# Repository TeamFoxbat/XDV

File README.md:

# XDV
100% digital-to-digital video encoder inspired by existing projects for the Original Xbox. Currently no firmware released but is compatible with existing digital video encoding solutions.

## Installation Notes
The v1.0-1.4 Xbox boards have a big electrolytic cap next to the stock encoder that will interfere with installation. Recommendation is to replace with a S1206 10uF ceramic.

The ferite bead on the bottom right of the stock encoder must be removed. 

Notes for installing the power and SMBus harnesses to come soon.

## Status Update
The Rev B board (not available here) does successfully take MakeMHz XboxHD+ firmware but has some visual glitches likely due to the flex PCB (not publicly available yet). Further work needs to be done to determine the cause but it's likely the flex.

The Rev C offers some minor improvements to reduce impedence mismatch on the TMDS traces but has not been ordered, a minor improvement to get closer to the spec.

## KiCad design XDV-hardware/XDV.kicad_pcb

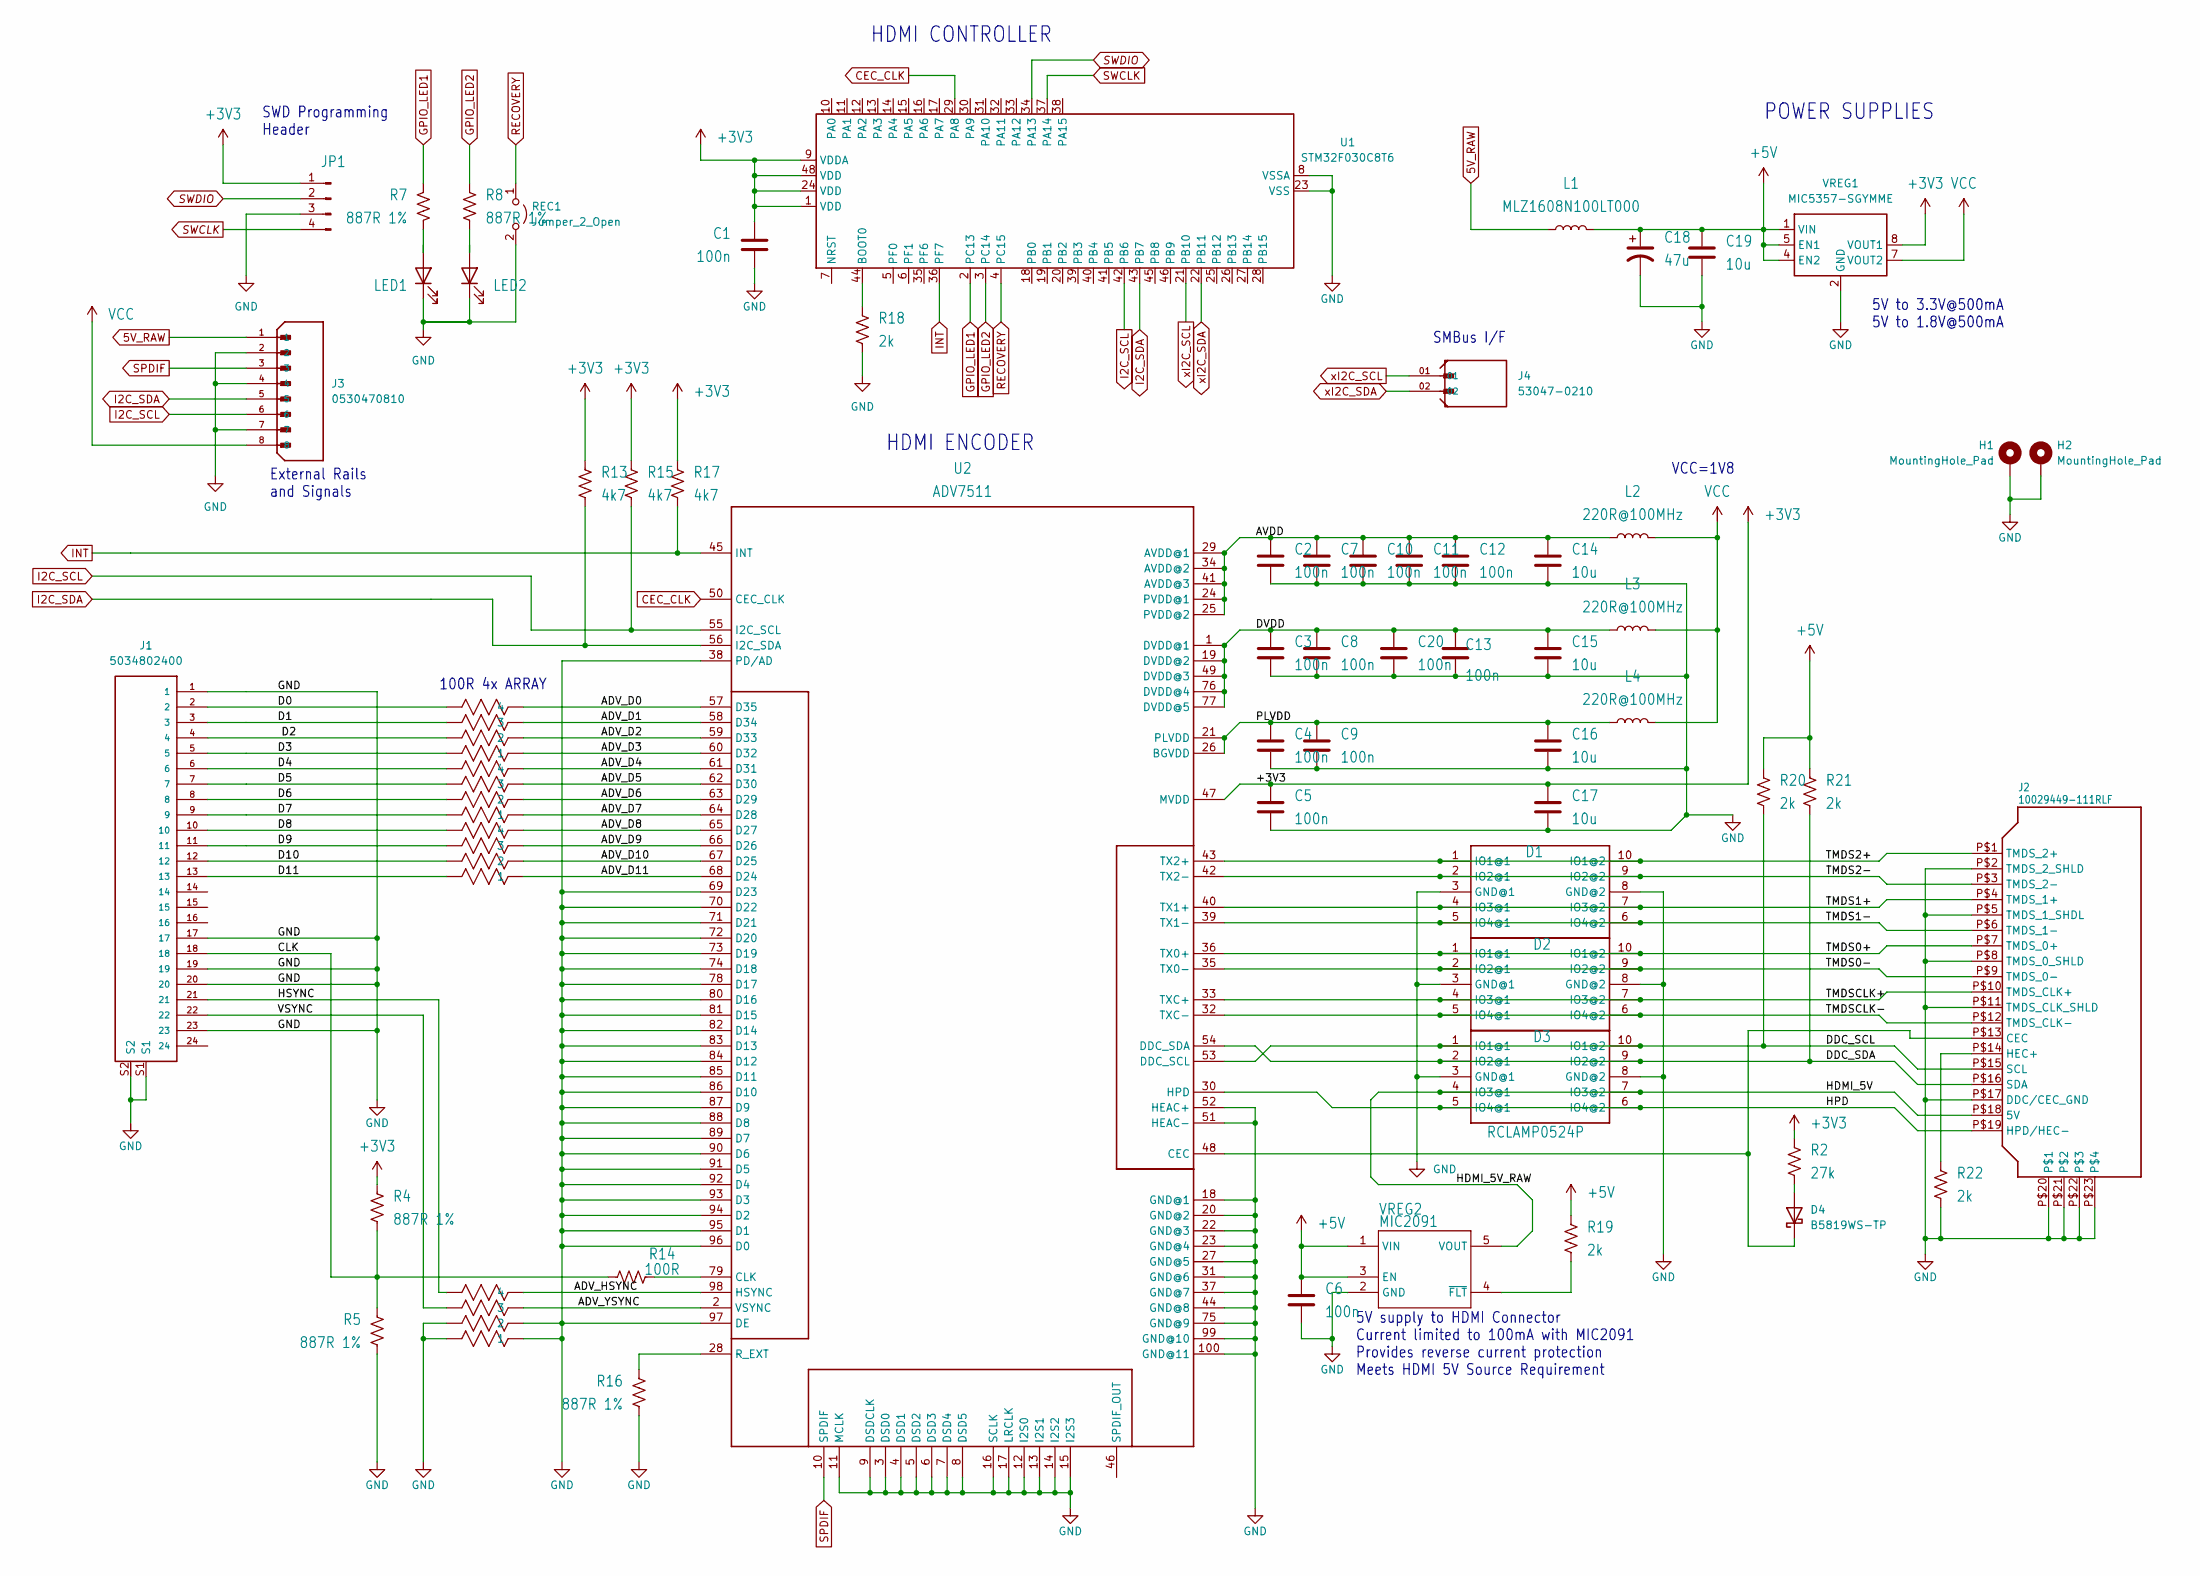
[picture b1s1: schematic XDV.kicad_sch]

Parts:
C1, C2, C3, C4, C5, C6, C7, C8, C9, C10, C11, C12, C13, C20: 100n; C_0402_1005Metric
C14, C15, C16, C17, C19: 10u; C_0603_1608Metric
C18: 47u; C_1206_3216Metric
D1, D2, D3: RCLAMP0524P; DIO_RCLAMP0524PATCT
D4: B5819WS-TP; D_SOD-323
H1, H2: MountingHole_Pad; MountingHole_4.3mm_M4_DIN965_Pad_TopBottom
J1: 5034802400; MOLEX_5034802400; PARTREV J
J2: 10029449-111RLF; HDMI_10029449
J3: 0530470810; MOLEX_0530470810; PARTREV B
J4: 53047-0210; MOLEX_53047-0210; PARTREV 04/19/2022
JP1: PINHD-1X5; PinSocket_1x04_P2.54mm_Vertical
L1: MLZ1608N100LT000; L_0603_1608Metric
L2, L3, L4: 220R@100MHz; L_0603_1608Metric
LED1: 150060VS75000; LED_0603_1608Metric
LED2: 150060BS75000; LED_0603_1608Metric
R2: 27k; R_0402_1005Metric
R4, R5, R7, R8, R16: 887R 1%; R_0402_1005Metric
R9, R10, R11, R12: YC124-JR-0733RL; R_Array_Convex_4x0402
R13, R15, R17: 4k7; R_0402_1005Metric
R14: 100R; R_0402_1005Metric
R18, R19, R20, R21, R22: 2k; R_0402_1005Metric
REC1: Jumper_2_Open; SolderJumper-2_P1.3mm_Open_Pad1.0x1.5mm
U1: STM32F030C8T6; LQFP-48_7x7mm_P0.5mm
U2: ADV7511; LQFP-100_14x14mm_P0.5mm
VREG1: MIC5357-SGYMME; MSOP-8-1EP_3x3mm_P0.65mm_EP2.5x3mm_Mask1.73x2.36mm_ThermalV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
VREG2: MIC2091; SOT-23-5

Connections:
5V_RAW: J3.1, L1.1
+3.3V: C1.1, C5.1, C17.1, JP1.1, R2.2, R4.2, R13.2, R15.2, R17.2, U1.1 (VDD), U1.9 (VDDA), U1.24 (VDD), U1.48 (VDD), U2.47 (MVDD), VREG1.8 (VOUT1)
+5V: C6.1, C18.1, C19.1, L1.2, R19.2, R20.2, R21.2, VREG1.1 (VIN), VREG1.4 (EN2), VREG1.5 (EN1), VREG2.1 (VIN), VREG2.3 (EN)
/ADV_D0: R9.4, U2.57 (D35)
/ADV_D1: R9.3, U2.58 (D34)
/ADV_D2: R9.2, U2.59 (D33)
/ADV_D3: R9.1, U2.60 (D32)
/ADV_D4: R10.4, U2.61 (D31)
/ADV_D5: R10.3, U2.62 (D30)
/ADV_D6: R10.2, U2.63 (D29)
/ADV_D7: R10.1, U2.64 (D28)
/ADV_D8: R11.4, U2.65 (D27)
/ADV_D9: R11.3, U2.66 (D26)
/ADV_D10: R11.2, U2.67 (D25)
/ADV_D11: R11.1, U2.68 (D24)
/ADV_HSYNC: R12.4, U2.98 (HSYNC)
/ADV_YSYNC: R12.3, U2.2 (VSYNC)
/AVDD: C2.1, C7.1, C10.1, C11.1, C12.1, C14.1, L2.1, U2.24 (PVDD@1), U2.25 (PVDD@2), U2.29 (AVDD@1), U2.34 (AVDD@2), U2.41 (AVDD@3)
/CLK: J1.18, R4.1, R5.2, R14.2
/D0: J1.2, R9.5
/D1: J1.3, R9.6
/D2: J1.4, R9.7
/D3: J1.5, R9.8
/D4: J1.6, R10.5
/D5: J1.7, R10.6
/D6: J1.8, R10.7
/D7: J1.9, R10.8
/D8: J1.10, R11.5
/D9: J1.11, R11.6
/D10: J1.12, R11.7
/D11: J1.13, R11.8
/DDC_SCL: D3.1 (IO1@1), D3.10 (IO1@2), J2.P$15 (SCL), R20.1, U2.53 (DDC_SCL)
/DDC_SDA: D3.2 (IO2@1), D3.9 (IO2@2), J2.P$16 (SDA), R21.1, U2.54 (DDC_SDA)
/DVDD: C3.1, C8.1, C13.1, C15.1, C20.1, L3.1, U2.1 (DVDD@1), U2.19 (DVDD@2), U2.49 (DVDD@3), U2.76 (DVDD@4), U2.77 (DVDD@5)
/HDMI_5V: D3.4 (IO3@1), D3.7 (IO3@2), J2.P$18 (5V), VREG2.5 (VOUT)
/HPD: D3.5 (IO4@1), D3.6 (IO4@2), J2.P$19 (HPD/HEC-), U2.30 (HPD)
/HSYNC: J1.21, R12.5
/PLVDD: C4.1, C9.1, C16.1, L4.1, U2.21 (PLVDD), U2.26 (BGVDD)
/TMDS0+: D2.1 (IO1@1), D2.10 (IO1@2), J2.P$7 (TMDS_0+), U2.36 (TX0+)
/TMDS0-: D2.2 (IO2@1), D2.9 (IO2@2), J2.P$9 (TMDS_0-), U2.35 (TX0-)
/TMDS1+: D1.4 (IO3@1), D1.7 (IO3@2), J2.P$4 (TMDS_1+), U2.40 (TX1+)
/TMDS1-: D1.5 (IO4@1), D1.6 (IO4@2), J2.P$6 (TMDS_1-), U2.39 (TX1-)
/TMDS2+: D1.1 (IO1@1), D1.10 (IO1@2), J2.P$1 (TMDS_2+), U2.43 (TX2+)
/TMDS2-: D1.2 (IO2@1), D1.9 (IO2@2), J2.P$3 (TMDS_2-), U2.42 (TX2-)
/TMDSCLK+: D2.4 (IO3@1), D2.7 (IO3@2), J2.P$10 (TMDS_CLK+), U2.33 (TXC+)
/TMDSCLK-: D2.5 (IO4@1), D2.6 (IO4@2), J2.P$12 (TMDS_CLK-), U2.32 (TXC-)
/VSYNC: J1.22, R12.6
CEC_CLK: U1.29 (PA8), U2.50 (CEC_CLK)
GND: C1.2, C2.2, C3.2, C4.2, C5.2, C6.2, C7.2, C8.2, C9.2, C10.2, C11.2, C12.2, C13.2, C14.2, C15.2, C16.2, C17.2, C18.2, C19.2, C20.2, D1.3 (GND@1), D1.8 (GND@2), D2.3 (GND@1), D2.8 (GND@2), D3.3 (GND@1), D3.8 (GND@2), H1.1, H2.1, J1.1, J1.17, J1.19, J1.20, J1.23, J1.S1, J1.S2, J2.P$2 (TMDS_2_SHLD), J2.P$5 (TMDS_1_SHDL), J2.P$8 (TMDS_0_SHLD), J2.P$11 (TMDS_CLK_SHLD), J2.P$17 (DDC/CEC_GND), J2.P$20, J2.P$21, J2.P$22, J2.P$23, J3.2, J3.4, J3.7, JP1.3, LED1.1 (K), LED2.1 (K), R5.1, R12.1, R12.2, R12.7, R12.8, R16.1, R18.1, R22.1, REC1.2 (B), U1.8 (VSSA), U1.23 (VSS), U1.47 (VSS), U2.3 (DSD0), U2.4 (DSD1), U2.5 (DSD2), U2.6 (DSD3), U2.7 (DSD4), U2.8 (DSD5), U2.9 (DSDCLK), U2.11 (MCLK), U2.12 (I2S0), U2.13 (I2S1), U2.14 (I2S2), U2.15 (I2S3), U2.16 (SCLK), U2.17 (LRCLK), U2.18 (GND@1), U2.20 (GND@2), U2.22 (GND@3), U2.23 (GND@4), U2.27 (GND@5), U2.31 (GND@6), U2.37 (GND@7), U2.38 (PD/AD), U2.44 (GND@8), U2.51 (HEAC-), U2.52 (HEAC+), U2.69 (D23), U2.70 (D22), U2.71 (D21), U2.72 (D20), U2.73 (D19), U2.74 (D18), U2.75 (GND@9), U2.78 (D17), U2.80 (D16), U2.81 (D15), U2.82 (D14), U2.83 (D13), U2.84 (D12), U2.85 (D11), U2.86 (D10), U2.87 (D9), U2.88 (D8), U2.89 (D7), U2.90 (D6), U2.91 (D5), U2.92 (D4), U2.93 (D3), U2.94 (D2), U2.95 (D1), U2.96 (D0), U2.97 (DE), U2.99 (GND@10), U2.100 (GND@11), VREG1.2 (GND), VREG1.9 (GND), VREG2.2 (GND)
GPIO_LED1: R7.2, U1.2 (PC13)
GPIO_LED2: R8.2, U1.3 (PC14)
I2C_SCL: J3.6, R15.1, U1.42 (PB6), U2.55 (I2C_SCL)
I2C_SDA: J3.5, R13.1, U1.43 (PB7), U2.56 (I2C_SDA)
INT: R17.1, U1.36 (PF7), U2.45 (INT)
unnamed: D4.2 (A), R2.1
unnamed: D4.1 (K), J2.P$13 (CEC), U2.48 (CEC)
unnamed: J2.P$14 (HEC+), R22.2
unnamed: LED1.2 (A), R7.1
unnamed: LED2.2 (A), R8.1
unnamed: R18.2, U1.44 (BOOT0)
unnamed: R14.1, U2.79 (CLK)
unnamed: R16.2, U2.28 (R_EXT)
unnamed: R19.1, VREG2.4 (~FLT)
RECOVERY: REC1.1 (A), U1.4 (PC15)
SPDIF: J3.3, U2.10 (SPDIF)
SWCLK: JP1.4, U1.37 (PA14)
SWDIO: JP1.2, U1.34 (PA13)
VCC: J3.8, L2.2, L3.2, L4.2, VREG1.7 (VOUT2)
xI2C_SCL: J4.01, U1.21 (PB10)
xI2C_SDA: J4.02, U1.22 (PB11)

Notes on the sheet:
5V supply to HDMI Connector Current limited to 100mA with MIC2091 Provides reverse current protection Meets HDMI 5V Source Requirement
VCC=1V8
SMBus I/F
HDMI CONTROLLER
POWER SUPPLIES
100R 4x ARRAY
5V to 3.3V@500mA 5V to 1.8V@500mA
HDMI ENCODER
SWD Programming Header
External Rails and Signals

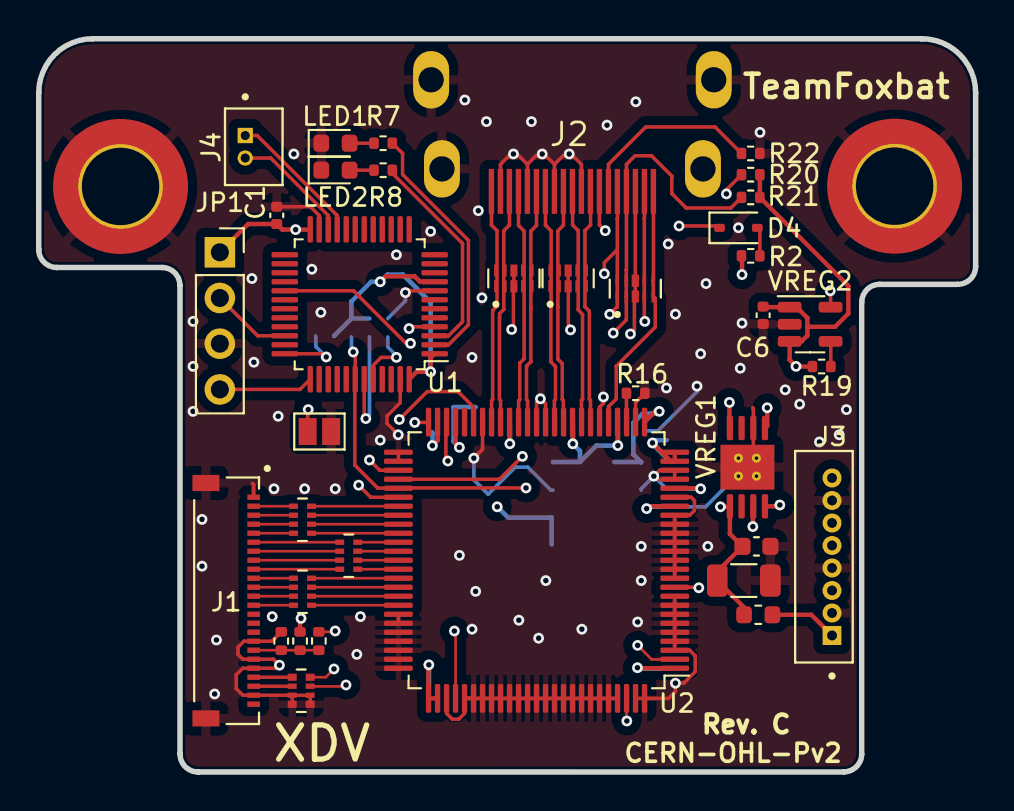
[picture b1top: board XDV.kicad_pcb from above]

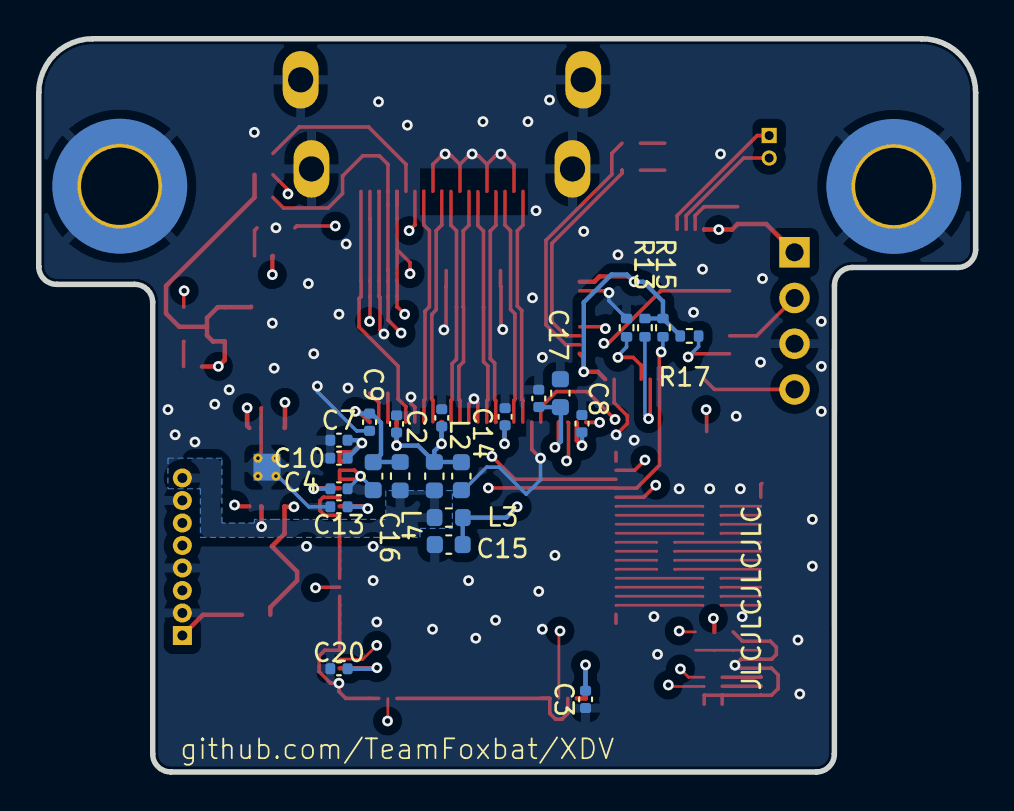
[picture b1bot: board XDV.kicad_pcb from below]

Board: 4 copper layers, 52.1 x 40.7 mm, 61 parts (23 on the bottom side), 70 nets.

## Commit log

2024-09-15 initial public commit

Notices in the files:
XDV-hardware/XDV.kicad_pcb:
CERN-OHL-Pv2
